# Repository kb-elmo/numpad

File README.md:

# numpad

[![CC BY-NC-SA 4.0][cc-by-nc-sa-shield]][cc-by-nc-sa]

This work is licensed under a
[Creative Commons Attribution-NonCommercial-ShareAlike 4.0 International License][cc-by-nc-sa].

[![CC BY-NC-SA 4.0][cc-by-nc-sa-image]][cc-by-nc-sa]

[cc-by-nc-sa]: http://creativecommons.org/licenses/by-nc-sa/4.0/
[cc-by-nc-sa-image]: https://licensebuttons.net/l/by-nc-sa/4.0/88x31.png
[cc-by-nc-sa-shield]: https://img.shields.io/badge/License-CC%20BY--NC--SA%204.0-lightgrey.svg

 simple numpad

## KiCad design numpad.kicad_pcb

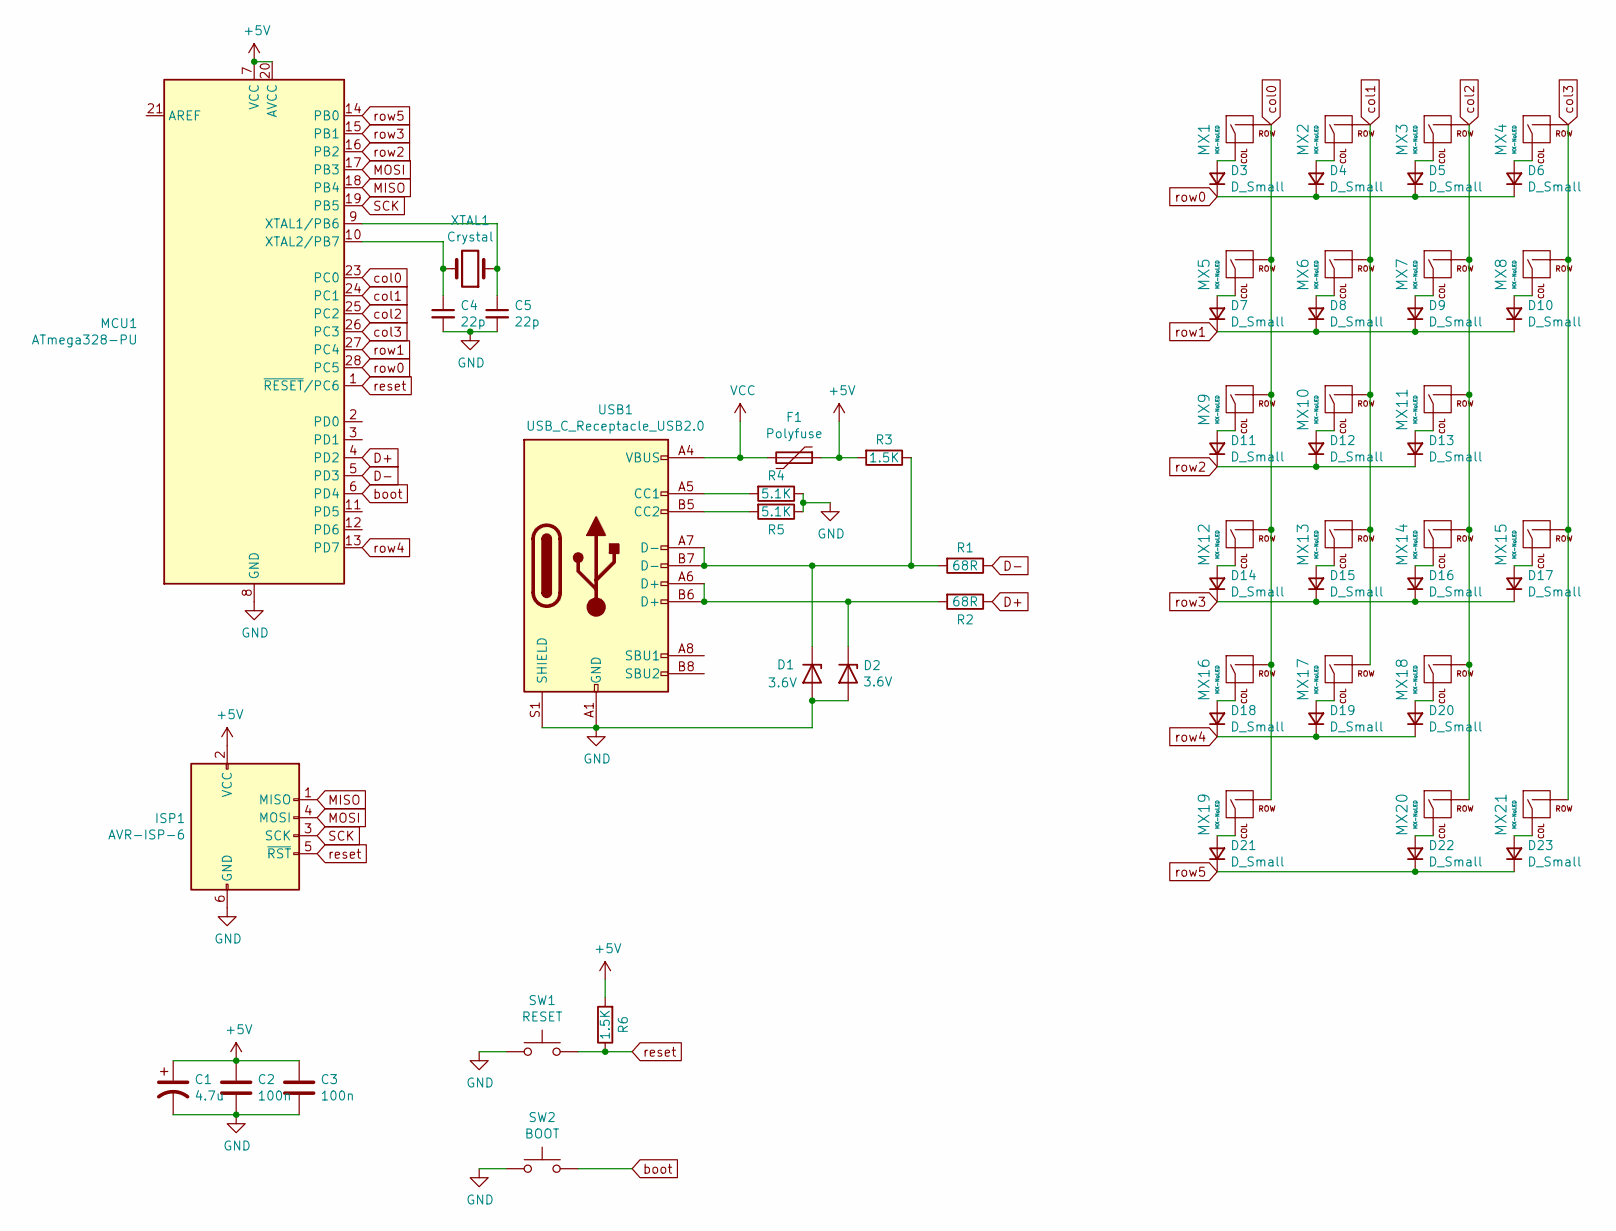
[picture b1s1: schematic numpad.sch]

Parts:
C1: 4.7u; CP_Radial_D4.0mm_P2.00mm
C2, C3: 100n; C_Disc_D5.0mm_W2.5mm_P2.50mm
C4, C5: 22p; C_Disc_D5.0mm_W2.5mm_P5.00mm
D1, D2: 3.6V; D_DO-35_SOD27_P7.62mm_Horizontal
D3, D4, D5, D6, D7, D8, D9, D10, D11, D12, D13, D14, D15, D16, D17, D18, D19, D20, D21, D22, D23: D_Small; D_DO-35_SOD27_P7.62mm_Horizontal
F1: Polyfuse; Fuse_Littelfuse_395Series
ISP1: AVR-ISP-6; PinHeader_2x03_P2.54mm_Horizontal
MCU1: ATmega328-PU; DIP-28_W7.62mm
MX1, MX2, MX3, MX4, MX5, MX6, MX7, MX8, MX9, MX10, MX11, MX12, MX13, MX14, MX16, MX17, MX18, MX20: MX-NoLED; MXOnly-1U-NoLED
MX15, MX19, MX21: MX-NoLED; MXOnly-2U-NoLED
R1, R2: 68R; R_Axial_DIN0204_L3.6mm_D1.6mm_P7.62mm_Horizontal
R3, R6: 1.5K; R_Axial_DIN0204_L3.6mm_D1.6mm_P7.62mm_Horizontal
R4, R5: 5.1K; R_Axial_DIN0204_L3.6mm_D1.6mm_P7.62mm_Horizontal
SW1: RESET; SW_PUSH_6mm
SW2: BOOT; SW_PUSH_6mm
USB1: USB_C_Receptacle_USB2.0; USB_C_GCT_USB4085
XTAL1: Crystal; Crystal_HC49-4H_Vertical

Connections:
+5V: C1.1, C2.1, C3.1, F1.1, ISP1.2 (VCC), MCU1.7 (VCC), MCU1.20 (AVCC), R3.2, R6.2
D+: MCU1.4 (PD2), R2.1
D-: MCU1.5 (PD3), R1.1
GND: C1.2, C2.2, C3.2, C4.2, C5.2, D1.2 (A), D2.2 (A), ISP1.6 (GND), MCU1.8 (GND), MCU1.22 (GND), R4.1, R5.1, SW1.1, SW2.1, USB1.A1 (GND), USB1.A12 (GND), USB1.B1 (GND), USB1.B12 (GND), USB1.S1 (SHIELD); also elsewhere on the board
MISO: ISP1.1 (MISO), MCU1.18 (PB4)
MOSI: ISP1.4 (MOSI), MCU1.17 (PB3)
unnamed: C4.1, MCU1.10 (XTAL2/PB7), XTAL1.2
unnamed: C5.1, MCU1.9 (XTAL1/PB6), XTAL1.1
unnamed: D1.1 (K), R1.2, R3.1, USB1.A7 (D-), USB1.B7 (D-)
unnamed: D2.1 (K), R2.2, USB1.A6 (D+), USB1.B6 (D+)
unnamed: D3.2 (A), MX1.1 (COL)
unnamed: D4.2 (A), MX2.1 (COL)
unnamed: D5.2 (A), MX3.1 (COL)
unnamed: D6.2 (A), MX4.1 (COL)
unnamed: D7.2 (A), MX5.1 (COL)
unnamed: D8.2 (A), MX6.1 (COL)
unnamed: D9.2 (A), MX7.1 (COL)
unnamed: D10.2 (A), MX8.1 (COL)
unnamed: D11.2 (A), MX9.1 (COL)
unnamed: D12.2 (A), MX10.1 (COL)
unnamed: D13.2 (A), MX11.1 (COL)
unnamed: D14.2 (A), MX12.1 (COL)
unnamed: D15.2 (A), MX13.1 (COL)
unnamed: D16.2 (A), MX14.1 (COL)
unnamed: D17.2 (A), MX15.1 (COL)
unnamed: D18.2 (A), MX16.1 (COL)
unnamed: D19.2 (A), MX17.1 (COL)
unnamed: D20.2 (A), MX18.1 (COL)
unnamed: D21.2 (A), MX19.1 (COL)
unnamed: D22.2 (A), MX20.1 (COL)
unnamed: D23.2 (A), MX21.1 (COL)
unnamed: R4.2, USB1.A5 (CC1)
unnamed: R5.2, USB1.B5 (CC2)
SCK: ISP1.3 (SCK), MCU1.19 (PB5)
VCC: F1.2, USB1.A4 (VBUS), USB1.A9 (VBUS), USB1.B4 (VBUS), USB1.B9 (VBUS)
boot: MCU1.6 (PD4), SW2.2; also elsewhere on the board
col0: MCU1.23 (PC0), MX1.2 (ROW), MX5.2 (ROW), MX9.2 (ROW), MX12.2 (ROW), MX16.2 (ROW), MX19.2 (ROW)
col1: MCU1.24 (PC1), MX2.2 (ROW), MX6.2 (ROW), MX10.2 (ROW), MX13.2 (ROW), MX17.2 (ROW)
col2: MCU1.25 (PC2), MX3.2 (ROW), MX7.2 (ROW), MX11.2 (ROW), MX14.2 (ROW), MX18.2 (ROW), MX20.2 (ROW)
col3: MCU1.26 (PC3), MX4.2 (ROW), MX8.2 (ROW), MX15.2 (ROW), MX21.2 (ROW)
reset: ISP1.5 (~RST), MCU1.1 (~RESET~/PC6), R6.1, SW1.2; also elsewhere on the board
row0: D3.1 (K), D4.1 (K), D5.1 (K), D6.1 (K), MCU1.28 (PC5)
row1: D7.1 (K), D8.1 (K), D9.1 (K), D10.1 (K), MCU1.27 (PC4)
row2: D11.1 (K), D12.1 (K), D13.1 (K), MCU1.16 (PB2)
row3: D14.1 (K), D15.1 (K), D16.1 (K), D17.1 (K), MCU1.15 (PB1)
row4: D18.1 (K), D19.1 (K), D20.1 (K), MCU1.13 (PD7)
row5: D21.1 (K), D22.1 (K), D23.1 (K), MCU1.14 (PB0)

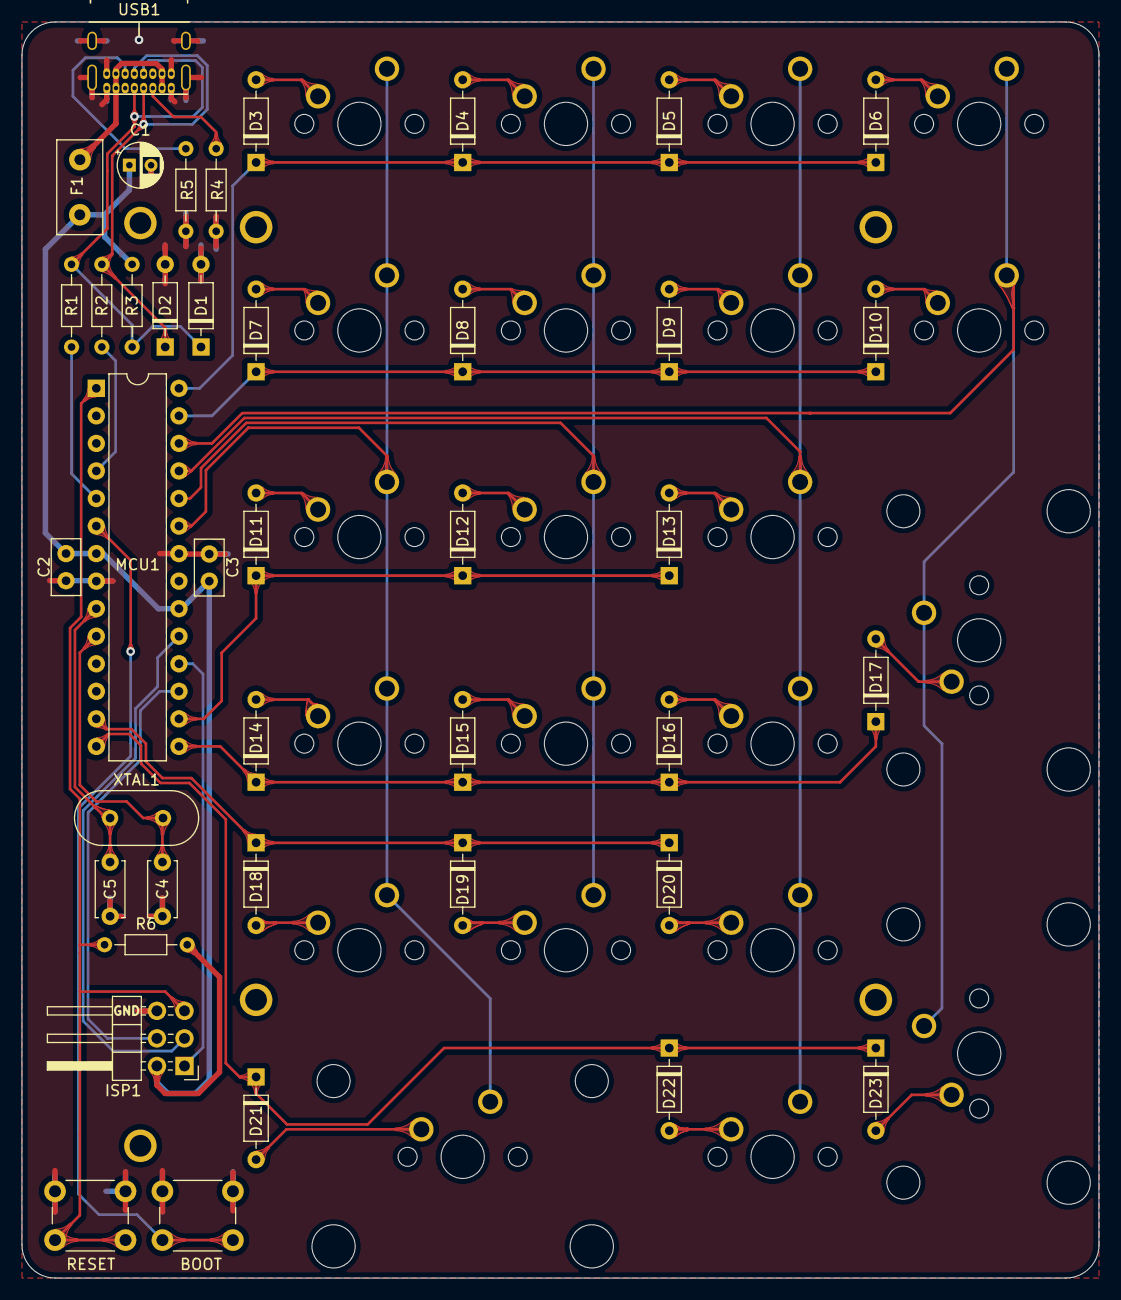
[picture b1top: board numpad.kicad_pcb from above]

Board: 2 copper layers, 99.3 x 115.8 mm, 62 parts (0 on the bottom side), 47 nets.

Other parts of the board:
BOOT: BOOT; SW_PUSH_6mm
RESET: RESET; SW_PUSH_6mm

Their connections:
GND: BOOT.1, RESET.1; also elsewhere on the board
boot: BOOT.2; also elsewhere on the board
reset: RESET.2; also elsewhere on the board

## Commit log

2020-06-15 finished
2020-06-16 fix mistakes
2020-06-16 ISP routing improvements
2020-06-16 add giant elmo logo
2020-07-11 Update LICENSE
2020-07-27 added extras
